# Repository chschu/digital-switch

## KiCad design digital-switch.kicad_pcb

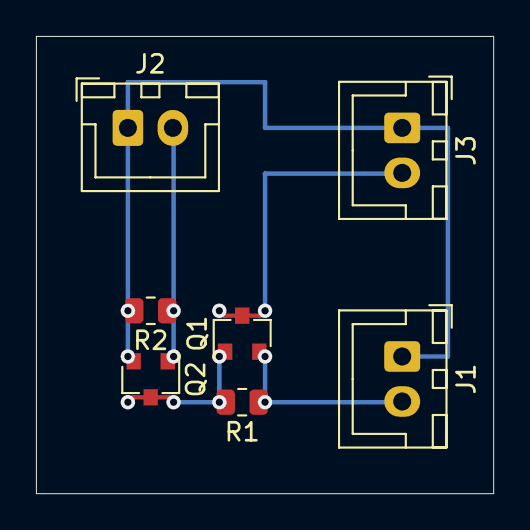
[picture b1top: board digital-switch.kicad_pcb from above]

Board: 2 copper layers, 25.4 x 25.4 mm, 7 parts (0 on the bottom side), 5 nets.

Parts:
J1, J2, J3: Conn_01x02_Male; JST_XH_B2B-XH-A_1x02_P2.50mm_Vertical
Q1: AO3401A; SOT-23
Q2: AO3402; SOT-23
R1, R2: 10k; R_0805_2012Metric

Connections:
/Vctl: J2.2, Q2.1, R2.1
/Vin: J1.2, Q1.2, R1.1
/Vout: J3.2, Q1.3
GND: J1.1, J2.1, J3.1, Q2.2, R2.2
unnamed: Q1.1, Q2.3, R1.2

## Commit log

2023-03-12 update to new KiCad format
